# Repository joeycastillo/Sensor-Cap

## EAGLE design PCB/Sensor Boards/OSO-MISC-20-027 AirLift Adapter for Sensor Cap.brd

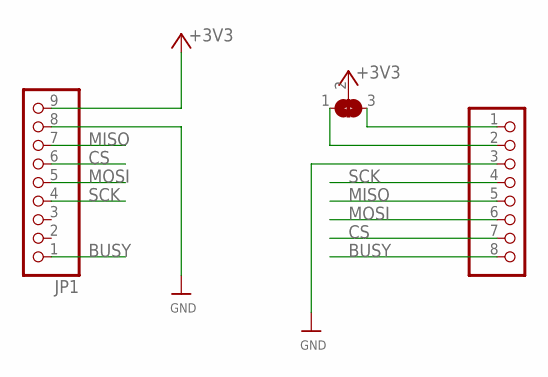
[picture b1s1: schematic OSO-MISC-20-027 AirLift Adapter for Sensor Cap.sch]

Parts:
JP1: HEADER-1X9_JSTSH; JST_SH9
JP2: PINHD-1X8/90; 1X08/90
SJ1: SOLDERJUMPER_2WAY; SOLDERJUMPER_2WAY_OPEN_NOPASTE

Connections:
+3V3: JP1.9, SJ1.2
BUSY: JP1.1, JP2.8
CS: JP1.6, JP2.7
GND: JP1.8, JP2.3
MISO: JP1.7, JP2.5
MOSI: JP1.5, JP2.6
unnamed: JP2.2, SJ1.1
unnamed: JP2.1, SJ1.3
SCK: JP1.4, JP2.4

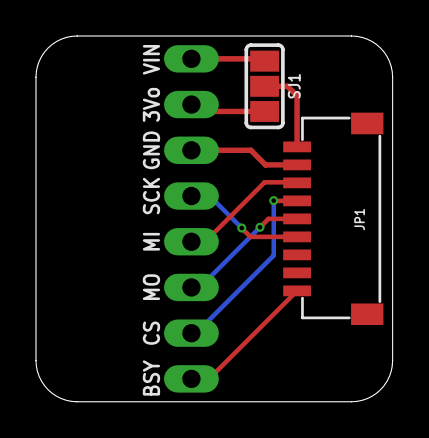
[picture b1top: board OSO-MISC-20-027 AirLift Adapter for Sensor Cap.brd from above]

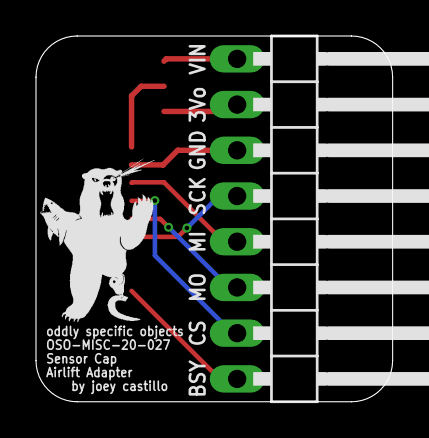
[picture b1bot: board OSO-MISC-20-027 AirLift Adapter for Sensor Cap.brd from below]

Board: 2 copper layers, 19.8 x 20.3 mm, 4 parts (2 on the bottom side), 9 nets.

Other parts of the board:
U$2: OSO_BEAR_250X360MIL_1000DPI

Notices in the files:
parts and their libraries:
microbuilder: This work is placed in the public domain, and may be freely used for commercial and non-commercial work with the following conditions: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
